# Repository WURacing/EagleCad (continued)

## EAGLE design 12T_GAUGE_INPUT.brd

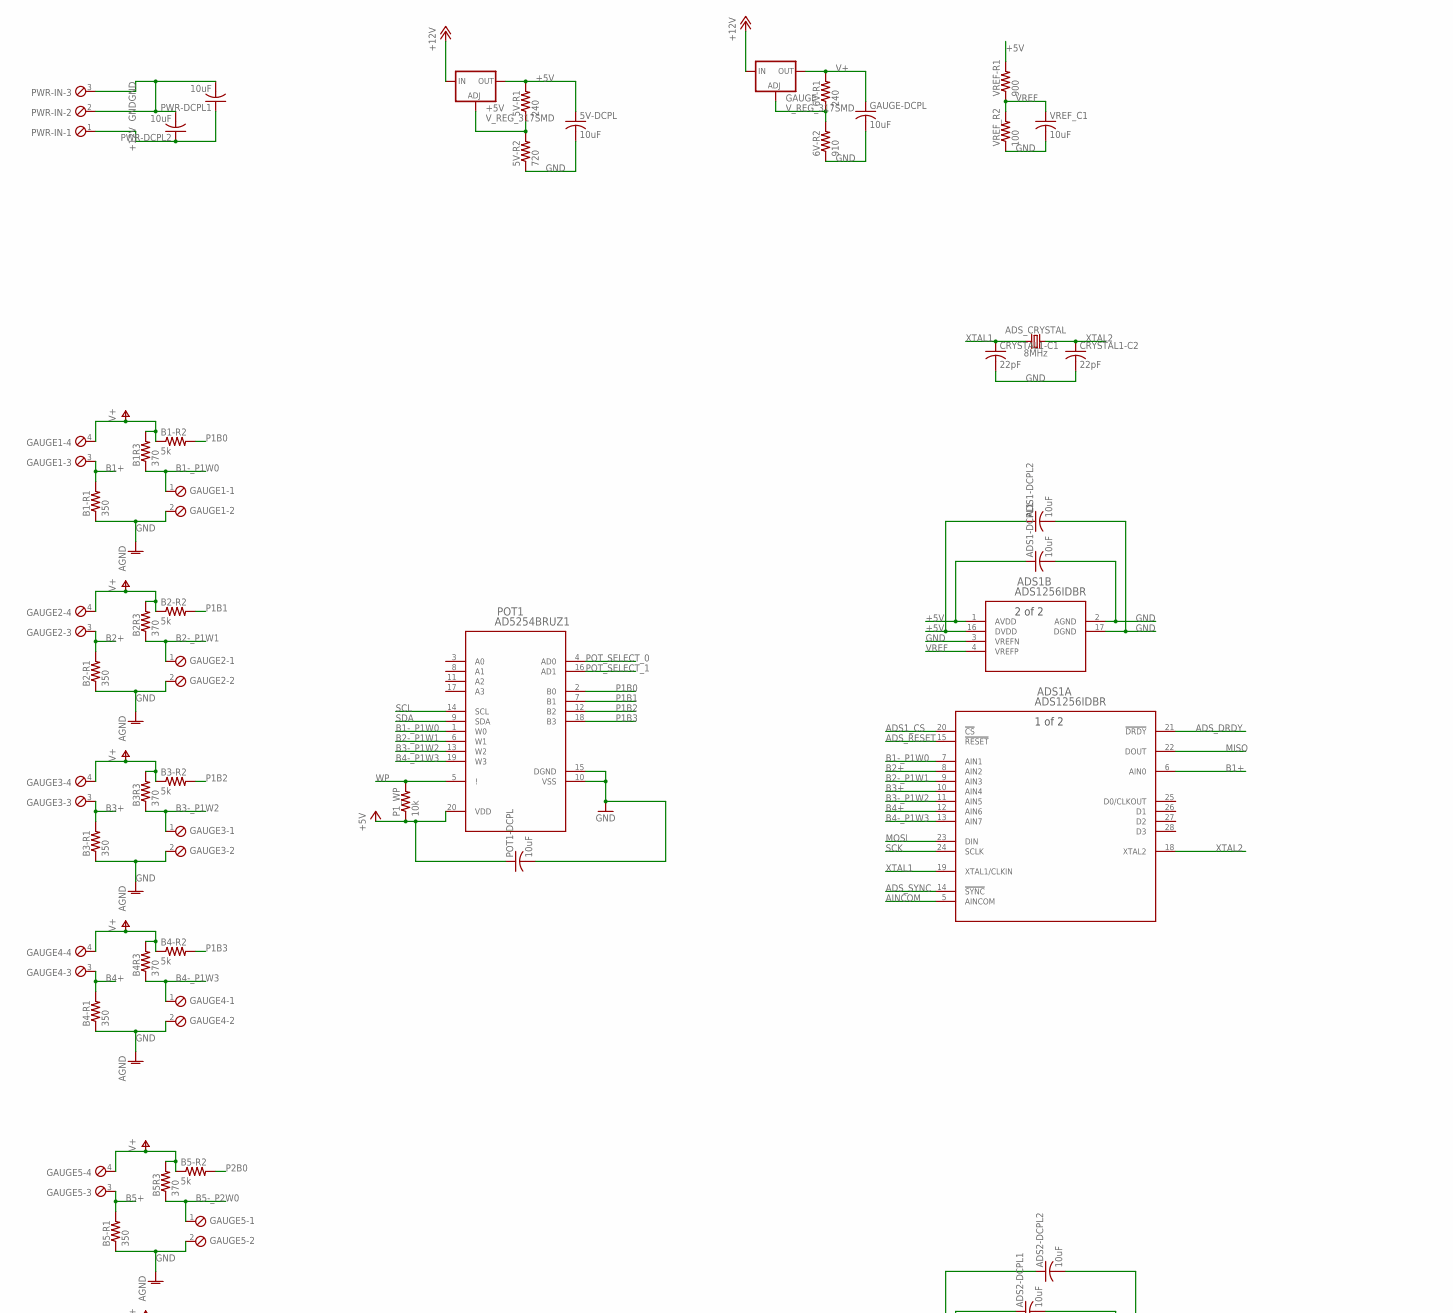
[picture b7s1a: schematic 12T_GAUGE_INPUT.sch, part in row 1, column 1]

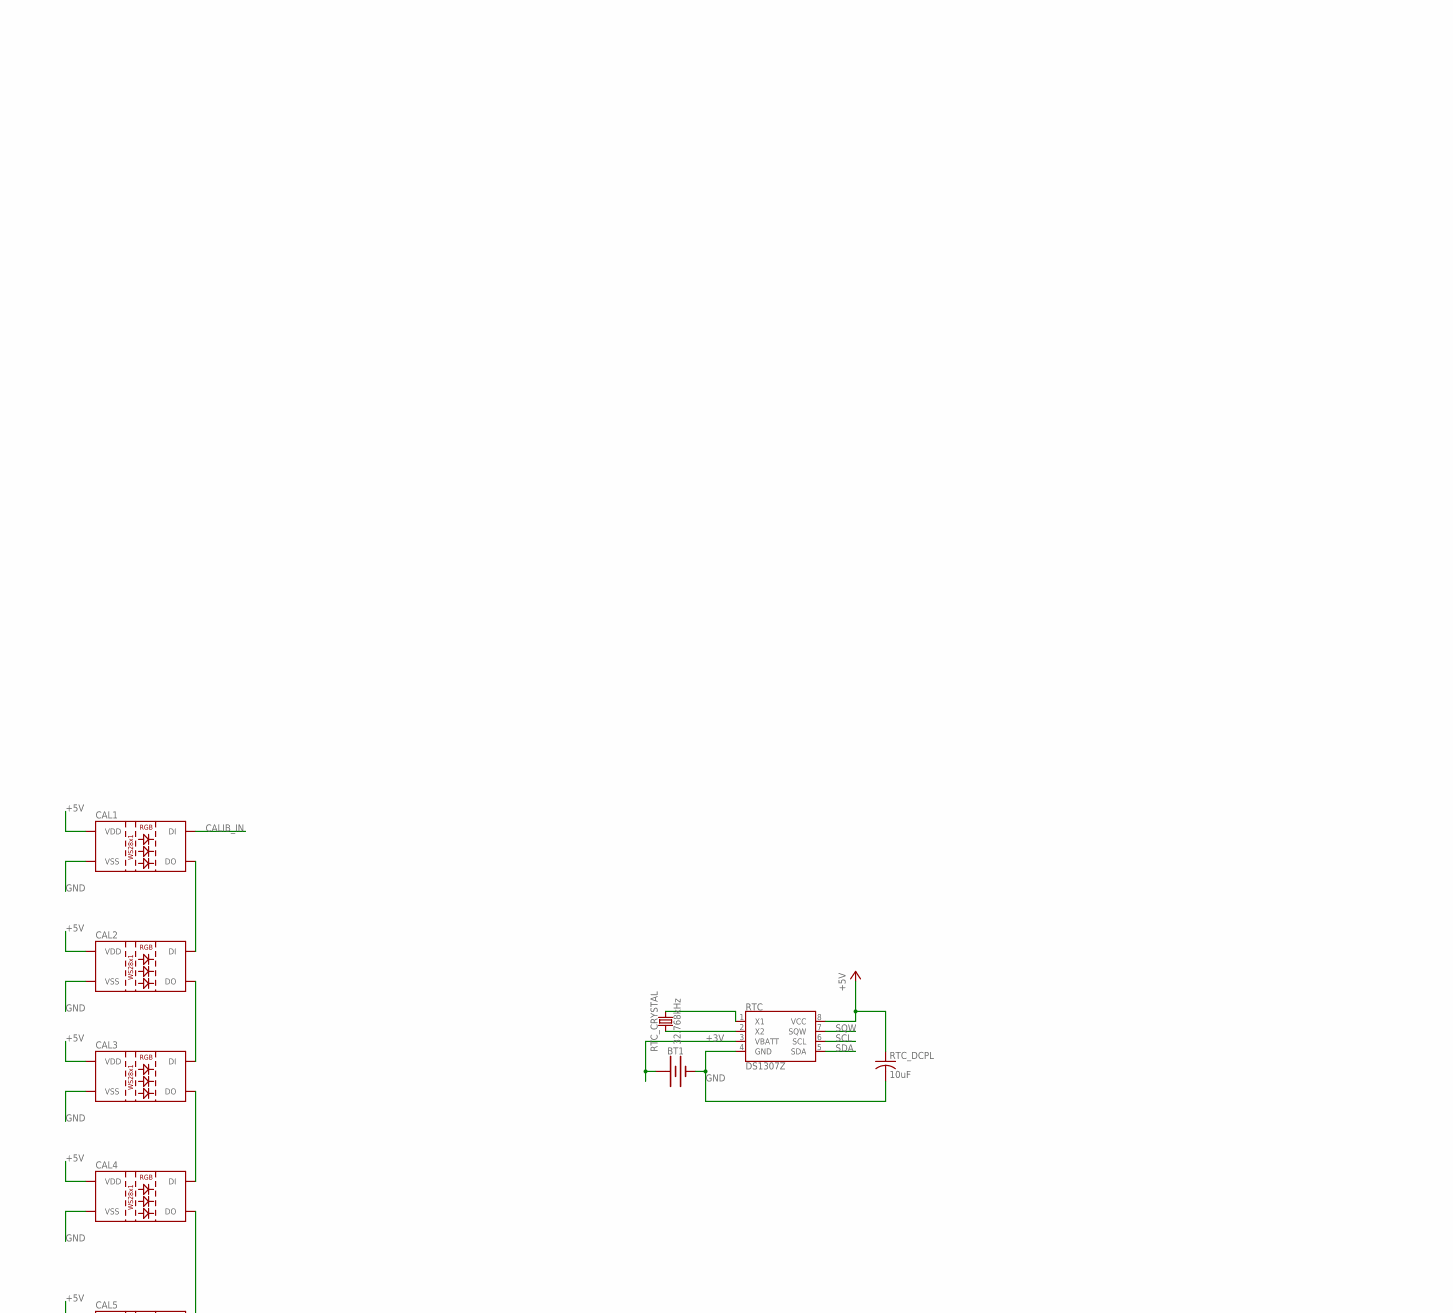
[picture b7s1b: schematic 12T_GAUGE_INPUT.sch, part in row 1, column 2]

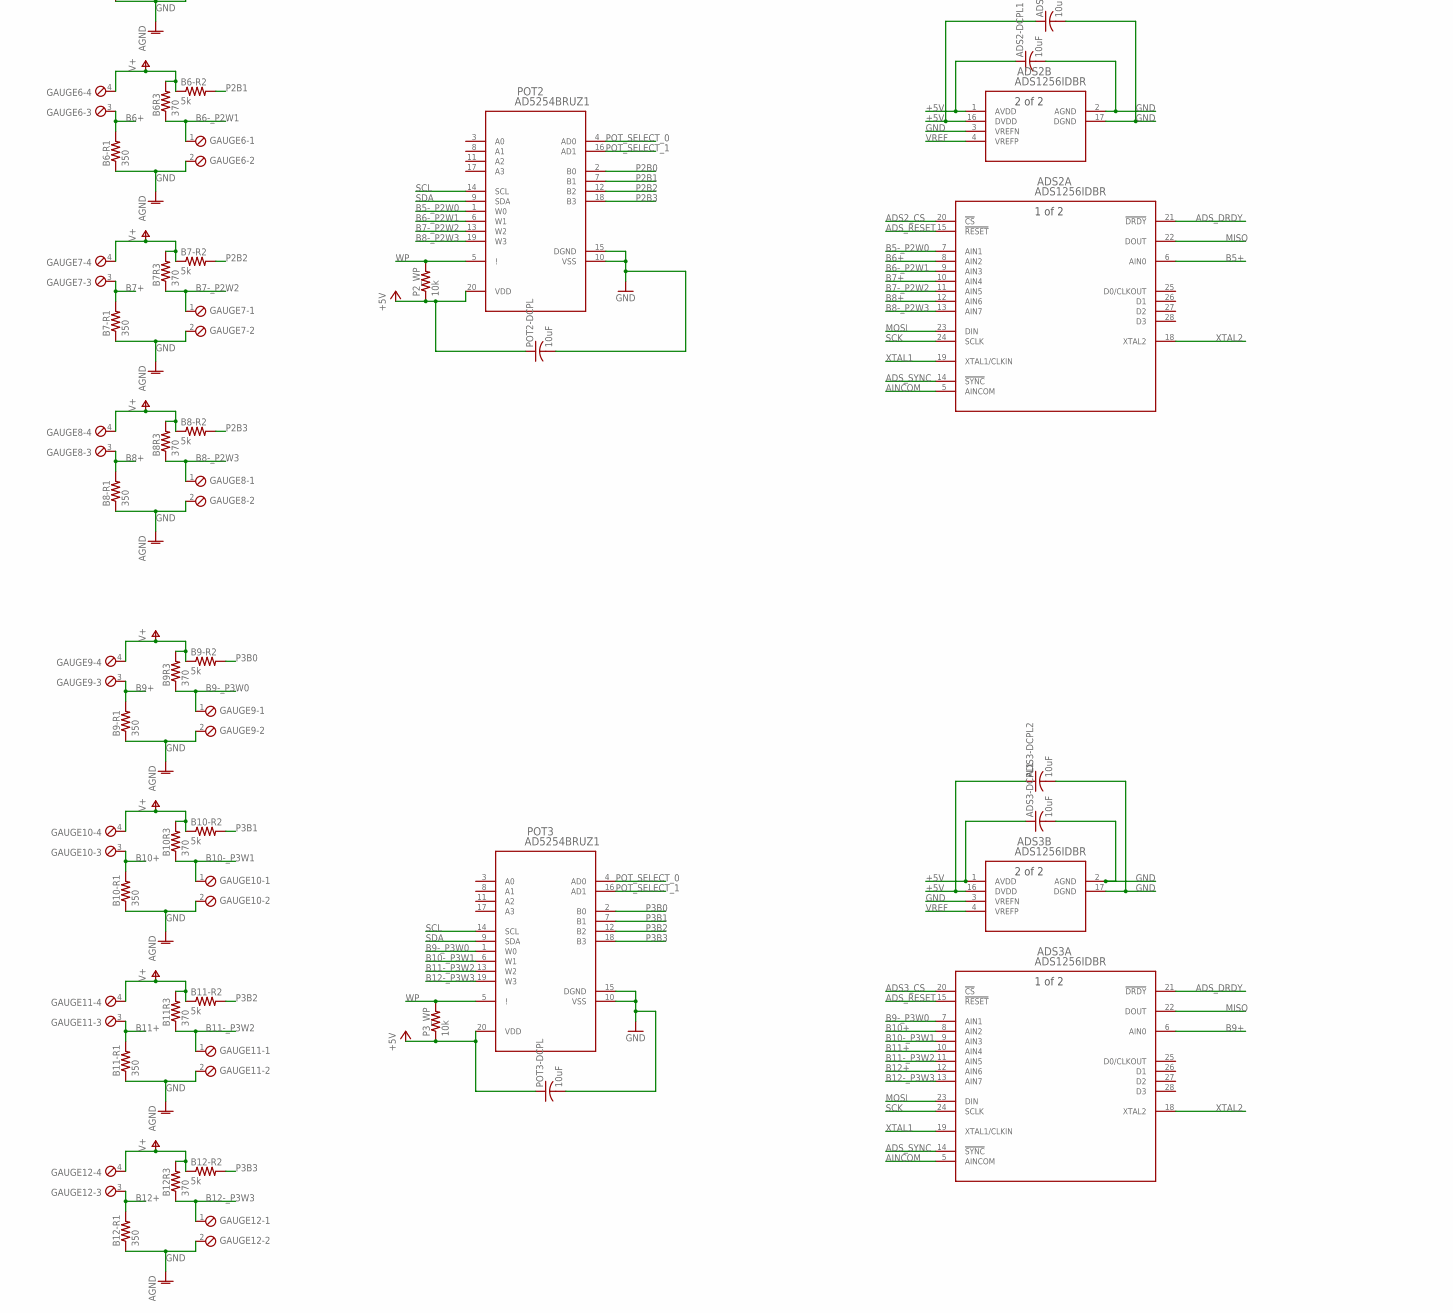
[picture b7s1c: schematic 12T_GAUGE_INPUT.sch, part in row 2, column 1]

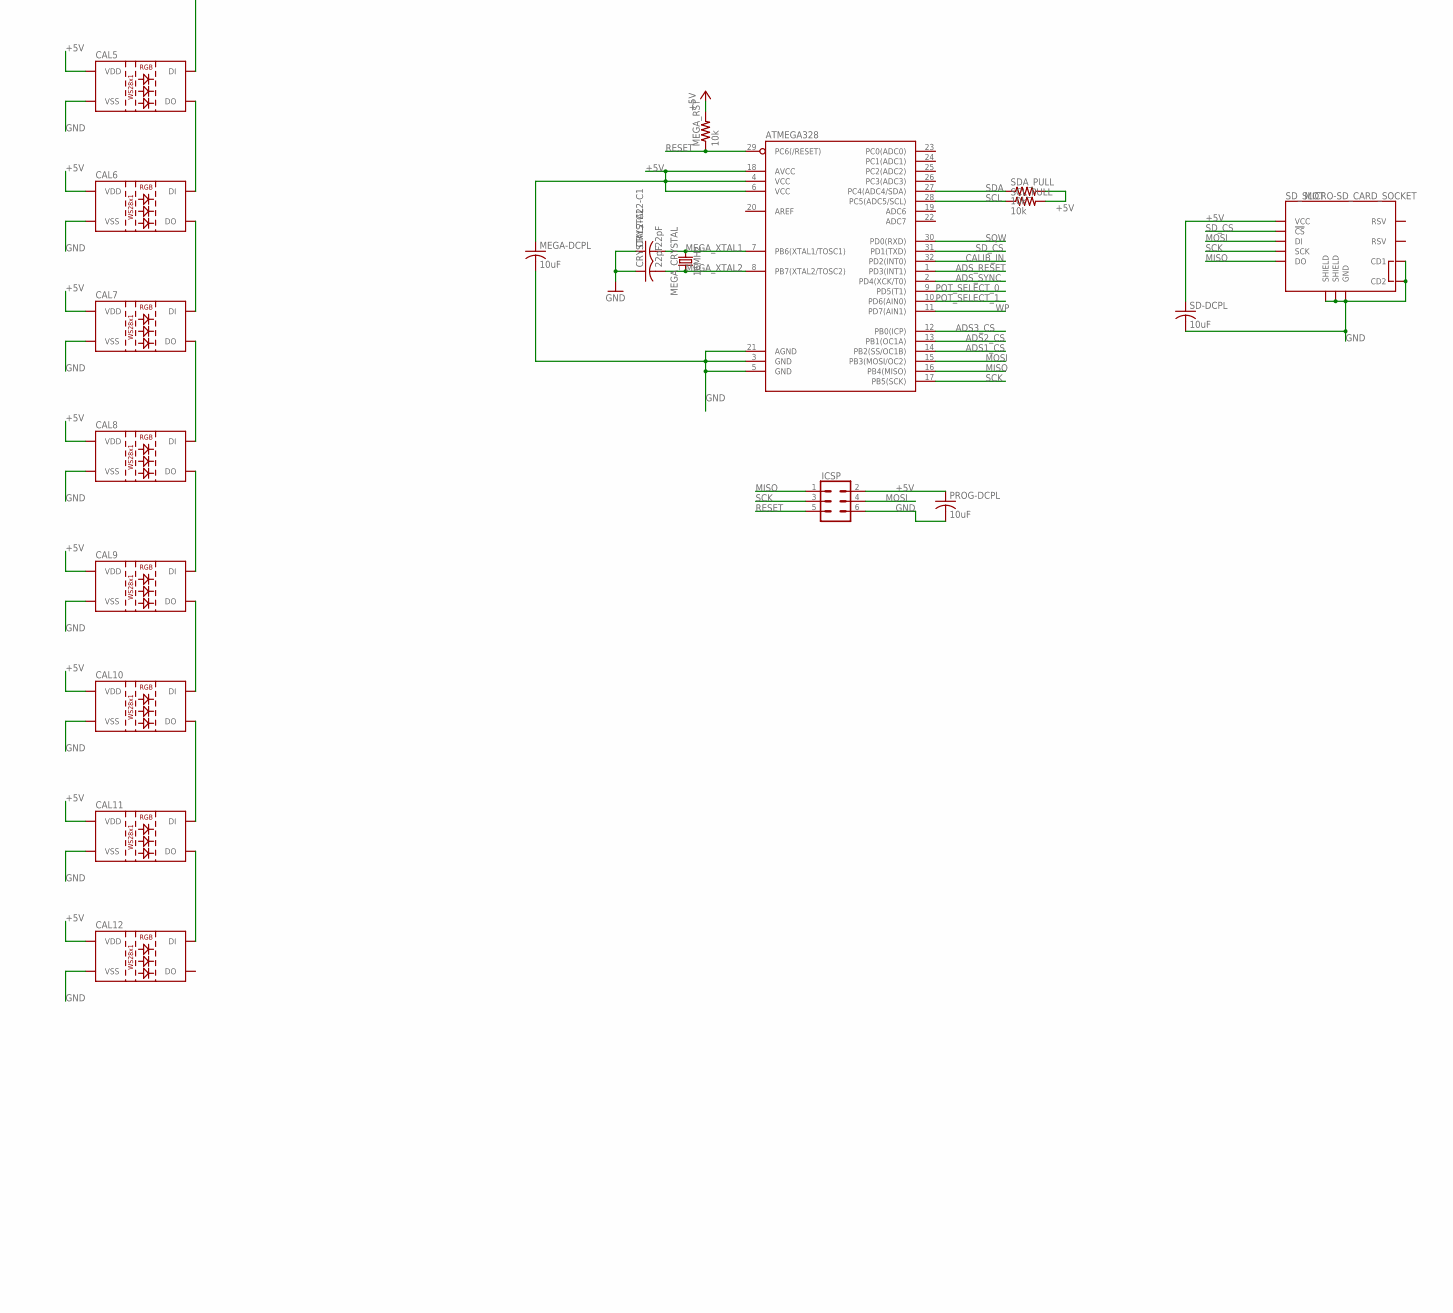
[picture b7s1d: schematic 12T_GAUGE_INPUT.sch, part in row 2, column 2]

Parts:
5V-DCPL: 10uF; C1206
5V-R1, 6V-R1: 240; R1206
5V-R2: 720; R1206
6V-R2: 910; R1206
+5V: V_REG_317SMD; SOT223
ADS1, ADS2, ADS3: ADS1256IDBR; DB28
ADS1-DCPL1, ADS1-DCPL2, ADS2-DCPL1, ADS2-DCPL2, ADS3-DCPL1, ADS3-DCPL2: 10uF; C1206
ADS_CRYSTAL: 8MHz; CRYSTAL-SMD-5X3.2-4PAD
ATMEGA328: ATMEGA328P_TQFP; TQFP32-08
B1-R1, B2-R1, B3-R1, B4-R1, B5-R1, B6-R1, B7-R1, B8-R1, B9-R1, B10-R1, B11-R1, B12-R1: 350; R1206
B1-R2, B2-R2, B3-R2, B4-R2, B5-R2, B6-R2, B7-R2, B8-R2, B9-R2, B10-R2, B11-R2, B12-R2: 5k; R1206
B1R3, B2R3, B3R3, B4R3, B5R3, B6R3, B7R3, B8R3, B9R3, B10R3, B11R3, B12R3: 370; R1206
BT1: BATTERY-12MM_SMD; BATTCON_12MM
CAL1, CAL2, CAL3, CAL4, CAL5, CAL6, CAL7, CAL8, CAL9, CAL10, CAL11, CAL12: WS2812"; LED-TRICOLOR-5050-IC
CRYSTAL1-C1, CRYSTAL1-C2, CRYSTAL2-C1, CRYSTAL2-C2: 22pF; C1206
GAUGE: V_REG_317SMD; SOT223
GAUGE1, GAUGE2, GAUGE3, GAUGE4, GAUGE5, GAUGE6, GAUGE7, GAUGE8, GAUGE9, GAUGE10, GAUGE11, GAUGE12: MPT4; 4POL254
GAUGE-DCPL: 10uF; C1206
ICSP: CONN_03X2FEMALE_SMD; 2X3_SMD
MEGA-DCPL: 10uF; C1206
MEGA_CRYSTAL: 16MHz; CRYSTAL-SMD-5X3.2-4PAD
MEGA_RST: 10k; R1206
P1_WP, P2_WP, P3_WP: 10k; R1206
POT1, POT2, POT3: AD5254BRUZ1; RU_20
POT1-DCPL, POT2-DCPL, POT3-DCPL: 10uF; C1206
PROG-DCPL: 10uF; C1206
PWR-DCPL1, PWR-DCPL2: 10uF; C1206
PWR-IN: MPT3; 3POL254
RTC: DS1307Z; SO08-0.15
RTC_CRYSTAL: 32.768kHz; CRYSTAL-SMD-3.2X1.5MM
RTC_DCPL: 10uF; C1206
SCL_PULL: 10k; R1206
SD-DCPL: 10uF; C1206
SDA_PULL: 10k; R1206
SD_SLOT: MICRO-SD_CARD_SOCKET; MICRO-SD-SOCKET
VREF-R1: 900; R1206
VREF_C1: 10uF; C1206
VREF_R2: 100; R1206

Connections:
+3V: BT1.PWR@1 (+), RTC.3 (VBATT)
+5V: 5V-DCPL.1, 5V-R1.2, +5V.2 (OUT), ADS1.1 (AVDD), ADS1.16 (DVDD), ADS1-DCPL1.1, ADS1-DCPL2.1, ADS2.1 (AVDD), ADS2.16 (DVDD), ADS2-DCPL1.1, ADS2-DCPL2.1, ADS3.1 (AVDD), ADS3.16 (DVDD), ADS3-DCPL1.1, ADS3-DCPL2.1, ATMEGA328.4 (VCC), ATMEGA328.6 (VCC), ATMEGA328.18 (AVCC), CAL1.3 (VDD), CAL1.5 (VDD), CAL2.3 (VDD), CAL2.5 (VDD), CAL3.3 (VDD), CAL3.5 (VDD), CAL4.3 (VDD), CAL4.5 (VDD), CAL5.3 (VDD), CAL5.5 (VDD), CAL6.3 (VDD), CAL6.5 (VDD), CAL7.3 (VDD), CAL7.5 (VDD), CAL8.3 (VDD), CAL8.5 (VDD), CAL9.3 (VDD), CAL9.5 (VDD), CAL10.3 (VDD), CAL10.5 (VDD), CAL11.3 (VDD), CAL11.5 (VDD), CAL12.3 (VDD), CAL12.5 (VDD), ICSP.2, MEGA-DCPL.1, MEGA_RST.2, P1_WP.1, P2_WP.1, P3_WP.1, POT1.20 (VDD), POT1-DCPL.1, POT2.20 (VDD), POT2-DCPL.1, POT3.20 (VDD), POT3-DCPL.1, PROG-DCPL.1, RTC.8 (VCC), RTC_DCPL.1, SCL_PULL.2, SD-DCPL.1, SDA_PULL.2, SD_SLOT.VCC, VREF-R1.2
+12V: +5V.3 (IN), GAUGE.3 (IN), PWR-DCPL1.1, PWR-DCPL2.1, PWR-IN.1
ADS1_CS: ADS1.20 (!CS), ATMEGA328.14 (PB2(SS/OC1B))
ADS2_CS: ADS2.20 (!CS), ATMEGA328.13 (PB1(OC1A))
ADS3_CS: ADS3.20 (!CS), ATMEGA328.12 (PB0(ICP))
ADS_DRDY: ADS1.21 (!DRDY), ADS2.21 (!DRDY), ADS3.21 (!DRDY)
ADS_RESET: ADS1.15 (!RESET), ADS2.15 (!RESET), ADS3.15 (!RESET), ATMEGA328.1 (PD3(INT1))
ADS_SYNC: ADS1.14 (!SYNC), ADS2.14 (!SYNC), ADS3.14 (!SYNC), ATMEGA328.2 (PD4(XCK/T0))
AINCOM: ADS1.5 (AINCOM), ADS2.5 (AINCOM), ADS3.5 (AINCOM)
B1+: ADS1.6 (AIN0), B1-R1.2, GAUGE1.3
B1-_P1W0: ADS1.7 (AIN1), B1R3.1, GAUGE1.1, POT1.1 (W0)
B2+: ADS1.8 (AIN2), B2-R1.2, GAUGE2.3
B2-_P1W1: ADS1.9 (AIN3), B2R3.1, GAUGE2.1, POT1.6 (W1)
B3+: ADS1.10 (AIN4), B3-R1.2, GAUGE3.3
B3-_P1W2: ADS1.11 (AIN5), B3R3.1, GAUGE3.1, POT1.13 (W2)
B4+: ADS1.12 (AIN6), B4-R1.2, GAUGE4.3
B4-_P1W3: ADS1.13 (AIN7), B4R3.1, GAUGE4.1, POT1.19 (W3)
B5+: ADS2.6 (AIN0), B5-R1.2, GAUGE5.3
B5-_P2W0: ADS2.7 (AIN1), B5R3.1, GAUGE5.1, POT2.1 (W0)
B6+: ADS2.8 (AIN2), B6-R1.2, GAUGE6.3
B6-_P2W1: ADS2.9 (AIN3), B6R3.1, GAUGE6.1, POT2.6 (W1)
B7+: ADS2.10 (AIN4), B7-R1.2, GAUGE7.3
B7-_P2W2: ADS2.11 (AIN5), B7R3.1, GAUGE7.1, POT2.13 (W2)
B8+: ADS2.12 (AIN6), B8-R1.2, GAUGE8.3
B8-_P2W3: ADS2.13 (AIN7), B8R3.1, GAUGE8.1, POT2.19 (W3)
B9+: ADS3.6 (AIN0), B9-R1.2, GAUGE9.3
B9-_P3W0: ADS3.7 (AIN1), B9R3.1, GAUGE9.1, POT3.1 (W0)
B10+: ADS3.8 (AIN2), B10-R1.2, GAUGE10.3
B10-_P3W1: ADS3.9 (AIN3), B10R3.1, GAUGE10.1, POT3.6 (W1)
B11+: ADS3.10 (AIN4), B11-R1.2, GAUGE11.3
B11-_P3W2: ADS3.11 (AIN5), B11R3.1, GAUGE11.1, POT3.13 (W2)
B12+: ADS3.12 (AIN6), B12-R1.2, GAUGE12.3
B12-_P3W3: ADS3.13 (AIN7), B12R3.1, GAUGE12.1, POT3.19 (W3)
CALIB_IN: ATMEGA328.32 (PD2(INT0)), CAL1.2 (DI)
GND: 5V-DCPL.2, 5V-R2.1, 6V-R2.1, ADS1.2 (AGND), ADS1.3 (VREFN), ADS1.17 (DGND), ADS1-DCPL1.2, ADS1-DCPL2.2, ADS2.2 (AGND), ADS2.3 (VREFN), ADS2.17 (DGND), ADS2-DCPL1.2, ADS2-DCPL2.2, ADS3.2 (AGND), ADS3.3 (VREFN), ADS3.17 (DGND), ADS3-DCPL1.2, ADS3-DCPL2.2, ATMEGA328.3 (GND), ATMEGA328.5 (GND), ATMEGA328.21 (AGND), B1-R1.1, B2-R1.1, B3-R1.1, B4-R1.1, B5-R1.1, B6-R1.1, B7-R1.1, B8-R1.1, B9-R1.1, B10-R1.1, B11-R1.1, B12-R1.1, BT1.GND (-), CAL1.6 (VSS), CAL2.6 (VSS), CAL3.6 (VSS), CAL4.6 (VSS), CAL5.6 (VSS), CAL6.6 (VSS), CAL7.6 (VSS), CAL8.6 (VSS), CAL9.6 (VSS), CAL10.6 (VSS), CAL11.6 (VSS), CAL12.6 (VSS), CRYSTAL1-C1.2, CRYSTAL1-C2.2, CRYSTAL2-C1.1, CRYSTAL2-C2.1, GAUGE1.2, GAUGE2.2, GAUGE3.2, GAUGE4.2, GAUGE5.2, GAUGE6.2, GAUGE7.2, GAUGE8.2, GAUGE9.2, GAUGE10.2, GAUGE11.2, GAUGE12.2, GAUGE-DCPL.2, ICSP.6, MEGA-DCPL.2, POT1.10 (VSS), POT1.15 (DGND), POT1-DCPL.2, POT2.10 (VSS), POT2.15 (DGND), POT2-DCPL.2, POT3.10 (VSS), POT3.15 (DGND), POT3-DCPL.2, PROG-DCPL.2, PWR-DCPL1.2, PWR-DCPL2.2, PWR-IN.2, PWR-IN.3, RTC.4 (GND), RTC_DCPL.2, SD-DCPL.2, SD_SLOT.CD1, SD_SLOT.CD2, SD_SLOT.GND, SD_SLOT.GND1 (SHIELD), SD_SLOT.GND3 (SHIELD), VREF_C1.2, VREF_R2.1
MEGA_XTAL1: ATMEGA328.7 (PB6(XTAL1/TOSC1)), CRYSTAL2-C1.2, MEGA_CRYSTAL.3 (2)
MEGA_XTAL2: ATMEGA328.8 (PB7(XTAL2/TOSC2)), CRYSTAL2-C2.2, MEGA_CRYSTAL.1
MISO: ADS1.22 (DOUT), ADS2.22 (DOUT), ADS3.22 (DOUT), ATMEGA328.16 (PB4(MISO)), ICSP.1, SD_SLOT.DO
MOSI: ADS1.23 (DIN), ADS2.23 (DIN), ADS3.23 (DIN), ATMEGA328.15 (PB3(MOSI/OC2)), ICSP.4, SD_SLOT.DI
unnamed: CAL1.1 (DO), CAL2.2 (DI)
unnamed: 5V-R1.1, 5V-R2.2, +5V.1 (ADJ)
unnamed: CAL2.1 (DO), CAL3.2 (DI)
unnamed: CAL3.1 (DO), CAL4.2 (DI)
unnamed: CAL4.1 (DO), CAL5.2 (DI)
unnamed: CAL5.1 (DO), CAL6.2 (DI)
unnamed: 6V-R1.1, 6V-R2.2, GAUGE.1 (ADJ)
unnamed: CAL6.1 (DO), CAL7.2 (DI)
unnamed: CAL7.1 (DO), CAL8.2 (DI)
unnamed: CAL8.1 (DO), CAL9.2 (DI)
unnamed: CAL9.1 (DO), CAL10.2 (DI)
unnamed: CAL10.1 (DO), CAL11.2 (DI)
unnamed: CAL11.1 (DO), CAL12.2 (DI)
unnamed: RTC.1 (X1), RTC_CRYSTAL.P$2 (2)
unnamed: RTC.2 (X2), RTC_CRYSTAL.P$1 (1)
P1B0: B1-R2.2, POT1.2 (B0)
P1B1: B2-R2.2, POT1.7 (B1)
P1B2: B3-R2.2, POT1.12 (B2)
P1B3: B4-R2.2, POT1.18 (B3)
P2B0: B5-R2.2, POT2.2 (B0)
P2B1: B6-R2.2, POT2.7 (B1)
P2B2: B7-R2.2, POT2.12 (B2)
P2B3: B8-R2.2, POT2.18 (B3)
P3B0: B9-R2.2, POT3.2 (B0)
P3B1: B10-R2.2, POT3.7 (B1)
P3B2: B11-R2.2, POT3.12 (B2)
P3B3: B12-R2.2, POT3.18 (B3)
POT_SELECT_0: ATMEGA328.9 (PD5(T1)), POT1.4 (AD0), POT2.4 (AD0), POT3.4 (AD0)
POT_SELECT_1: ATMEGA328.10 (PD6(AIN0)), POT1.16 (AD1), POT2.16 (AD1), POT3.16 (AD1)
RESET: ATMEGA328.29 (PC6(/RESET)), ICSP.5, MEGA_RST.1
SCK: ADS1.24 (SCLK), ADS2.24 (SCLK), ADS3.24 (SCLK), ATMEGA328.17 (PB5(SCK)), ICSP.3, SD_SLOT.SCLK (SCK)
SCL: ATMEGA328.28 (PC5(ADC5/SCL)), POT1.14 (SCL), POT2.14 (SCL), POT3.14 (SCL), RTC.6 (SCL), SCL_PULL.1
SDA: ATMEGA328.27 (PC4(ADC4/SDA)), POT1.9 (SDA), POT2.9 (SDA), POT3.9 (SDA), RTC.5 (SDA), SDA_PULL.1
SD_CS: ATMEGA328.31 (PD1(TXD)), SD_SLOT.CS (!CS)
SQW: ATMEGA328.30 (PD0(RXD)), RTC.7 (SQW)
V+: 6V-R1.2, B1-R2.1, B1R3.2, B2-R2.1, B2R3.2, B3-R2.1, B3R3.2, B4-R2.1, B4R3.2, B5-R2.1, B5R3.2, B6-R2.1, B6R3.2, B7-R2.1, B7R3.2, B8-R2.1, B8R3.2, B9-R2.1, B9R3.2, B10-R2.1, B10R3.2, B11-R2.1, B11R3.2, B12-R2.1, B12R3.2, GAUGE.2 (OUT), GAUGE1.4, GAUGE2.4, GAUGE3.4, GAUGE4.4, GAUGE5.4, GAUGE6.4, GAUGE7.4, GAUGE8.4, GAUGE9.4, GAUGE10.4, GAUGE11.4, GAUGE12.4, GAUGE-DCPL.1
VREF: ADS1.4 (VREFP), ADS2.4 (VREFP), ADS3.4 (VREFP), VREF-R1.1, VREF_C1.1, VREF_R2.2
WP: ATMEGA328.11 (PD7(AIN1)), P1_WP.2, P2_WP.2, P3_WP.2, POT1.5 (!), POT2.5 (!), POT3.5 (!)
XTAL1: ADS1.19 (XTAL1/CLKIN), ADS2.19 (XTAL1/CLKIN), ADS3.19 (XTAL1/CLKIN), ADS_CRYSTAL.1, CRYSTAL1-C1.1
XTAL2: ADS1.18 (XTAL2), ADS2.18 (XTAL2), ADS3.18 (XTAL2), ADS_CRYSTAL.3 (2), CRYSTAL1-C2.1

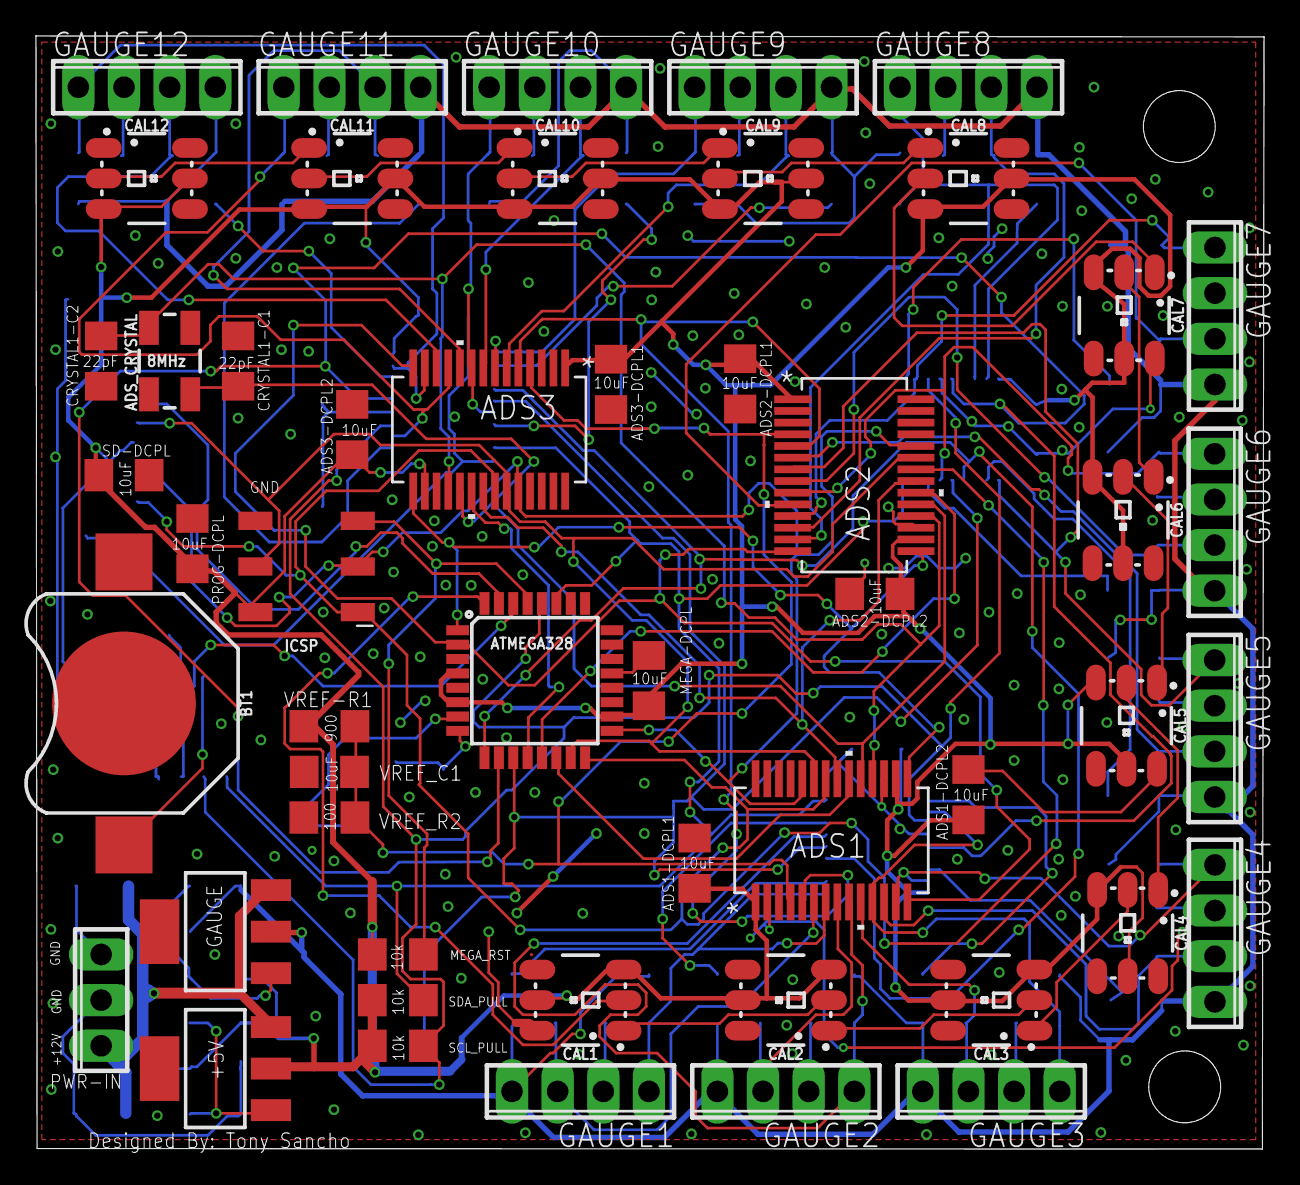
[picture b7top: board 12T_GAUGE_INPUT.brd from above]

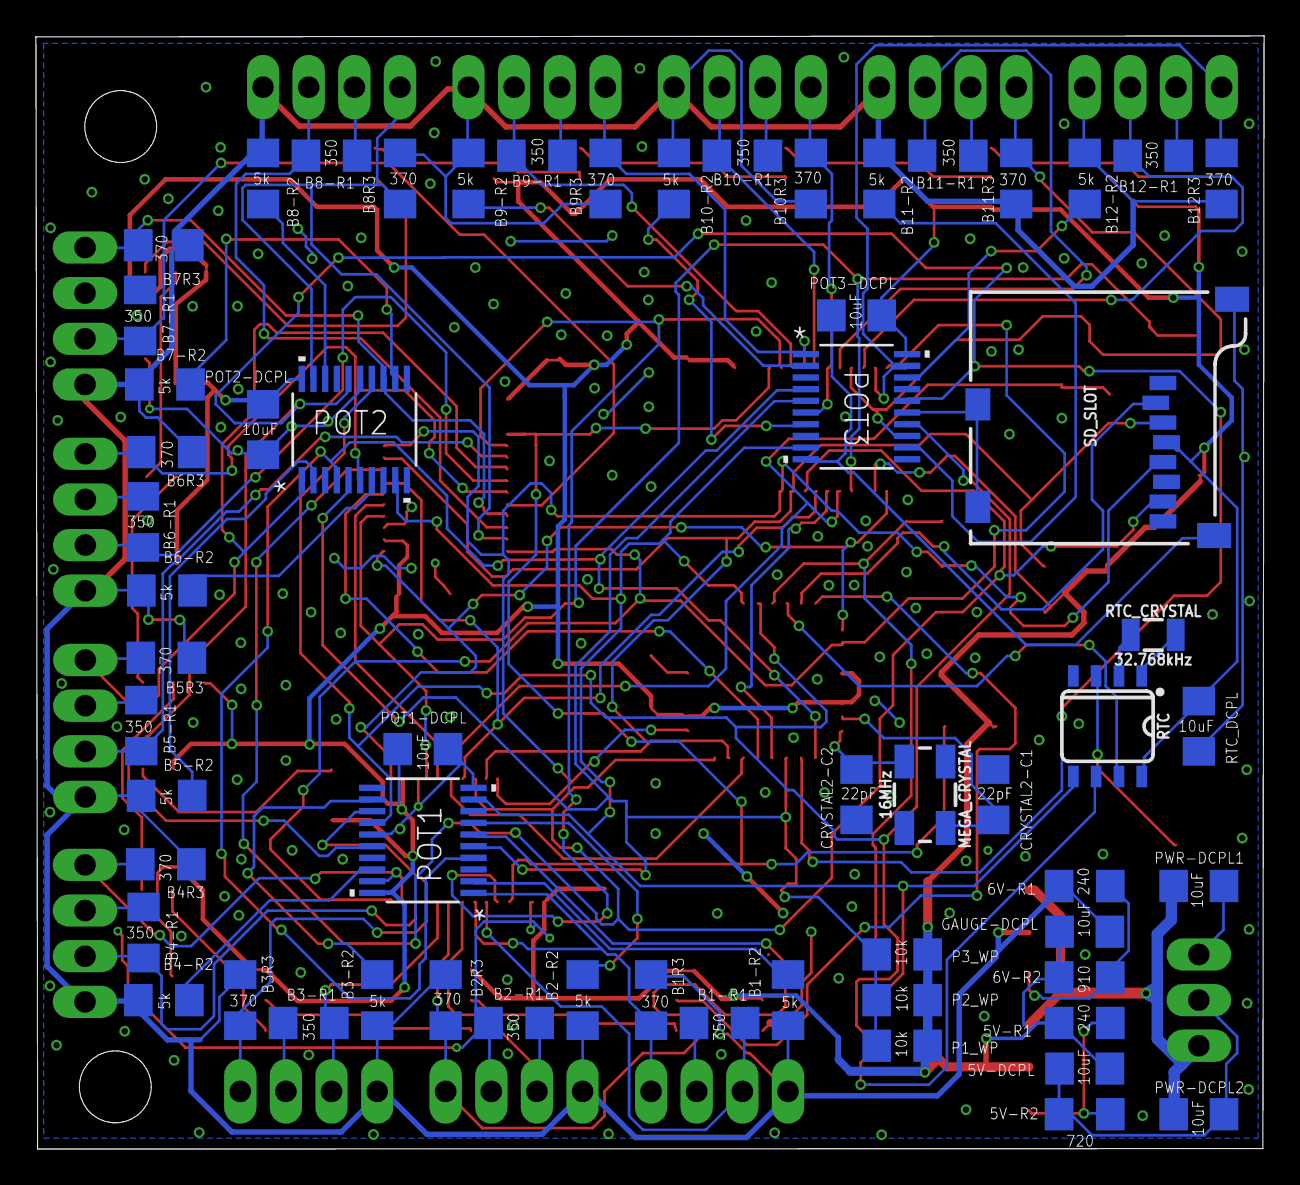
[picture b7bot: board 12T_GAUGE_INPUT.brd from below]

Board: 2 copper layers, 68.3 x 61.9 mm, 111 parts (60 on the bottom side), 80 nets.
